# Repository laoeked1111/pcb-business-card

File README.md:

# pcb-business-card

This is a PCB business card/ruler that I made. On the front is a QR code to my LinkedIn, a NFC chip to bring the user to a website, my contact information, 
and a imperial and metric ruler. On the back are some commonly used SMD footprints.

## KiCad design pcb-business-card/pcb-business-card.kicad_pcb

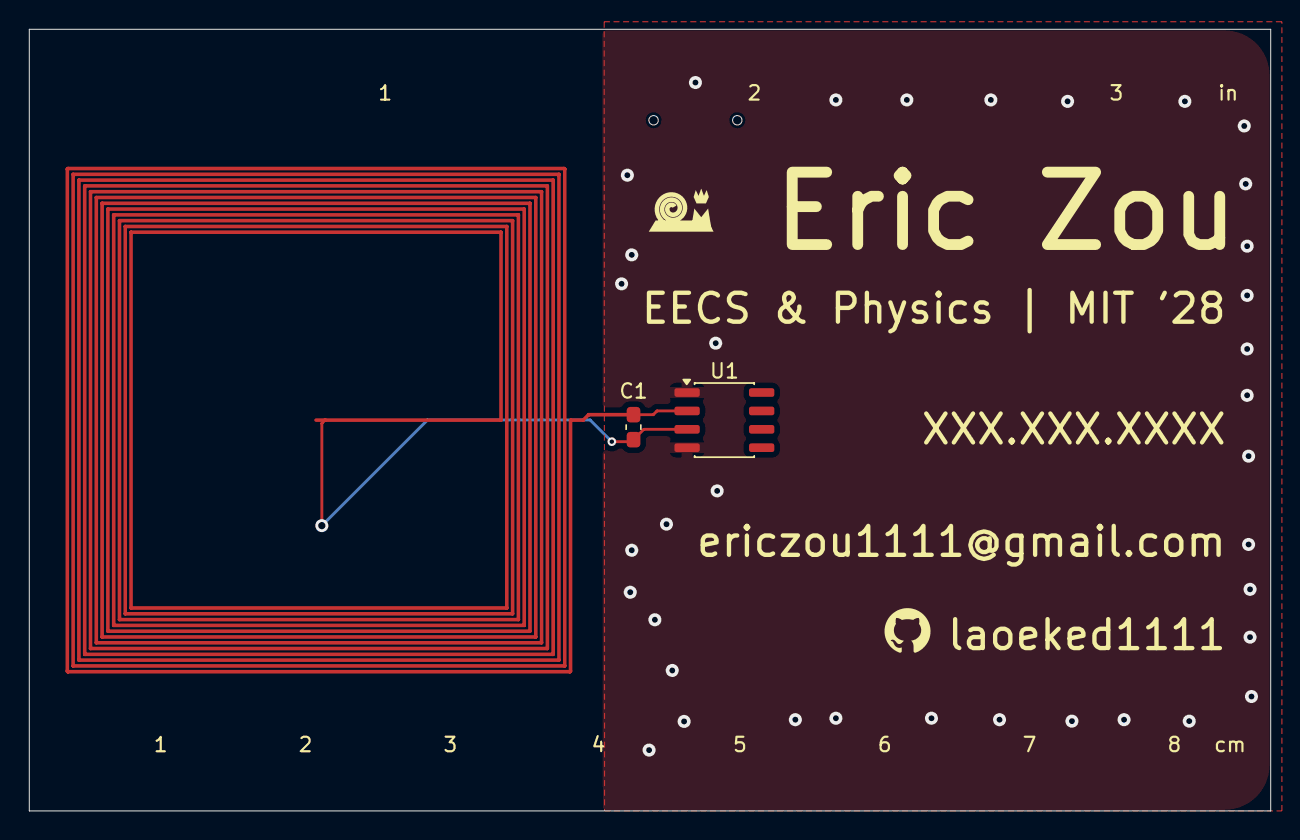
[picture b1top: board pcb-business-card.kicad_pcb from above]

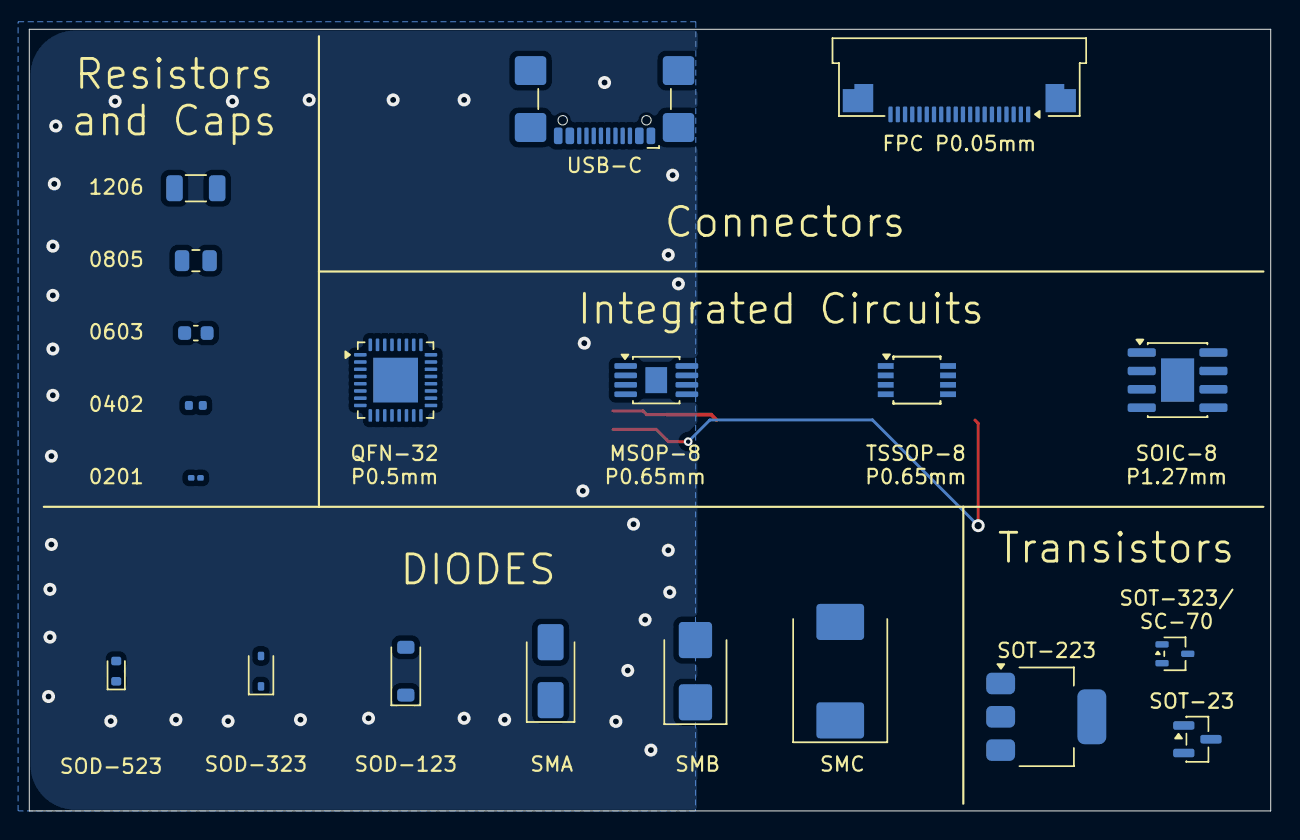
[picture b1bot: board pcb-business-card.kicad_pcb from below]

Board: 2 copper layers, 85.7 x 54.0 mm, 14 parts (11 on the bottom side), 3 nets.

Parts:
C1: C_TUNE; C_0603_1608Metric_Pad1.08x0.95mm_HandSolder
C2: C; C_0201_0603Metric
C3: C; C_0402_1005Metric
C4: C; C_0603_1608Metric
C5: C; C_0805_2012Metric
C6: C; C_1206_3216Metric
D1: D; D_SMA
D2: D; D_SMB
D3: D; D_SMC
D4: D; D_SOD-123
D5: D; D_SOD-323
D6: D; D_SOD-523
L1: 9.07u; rect_coil
U1: SO-8_3.9x4.9mm_P1.27mm

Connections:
GND: U1.1 (GND), U1.4 (GND)
unnamed: C1.1, L1.1, U1.2 (LA)
unnamed: C1.2, L1.2, U1.3 (LB)
